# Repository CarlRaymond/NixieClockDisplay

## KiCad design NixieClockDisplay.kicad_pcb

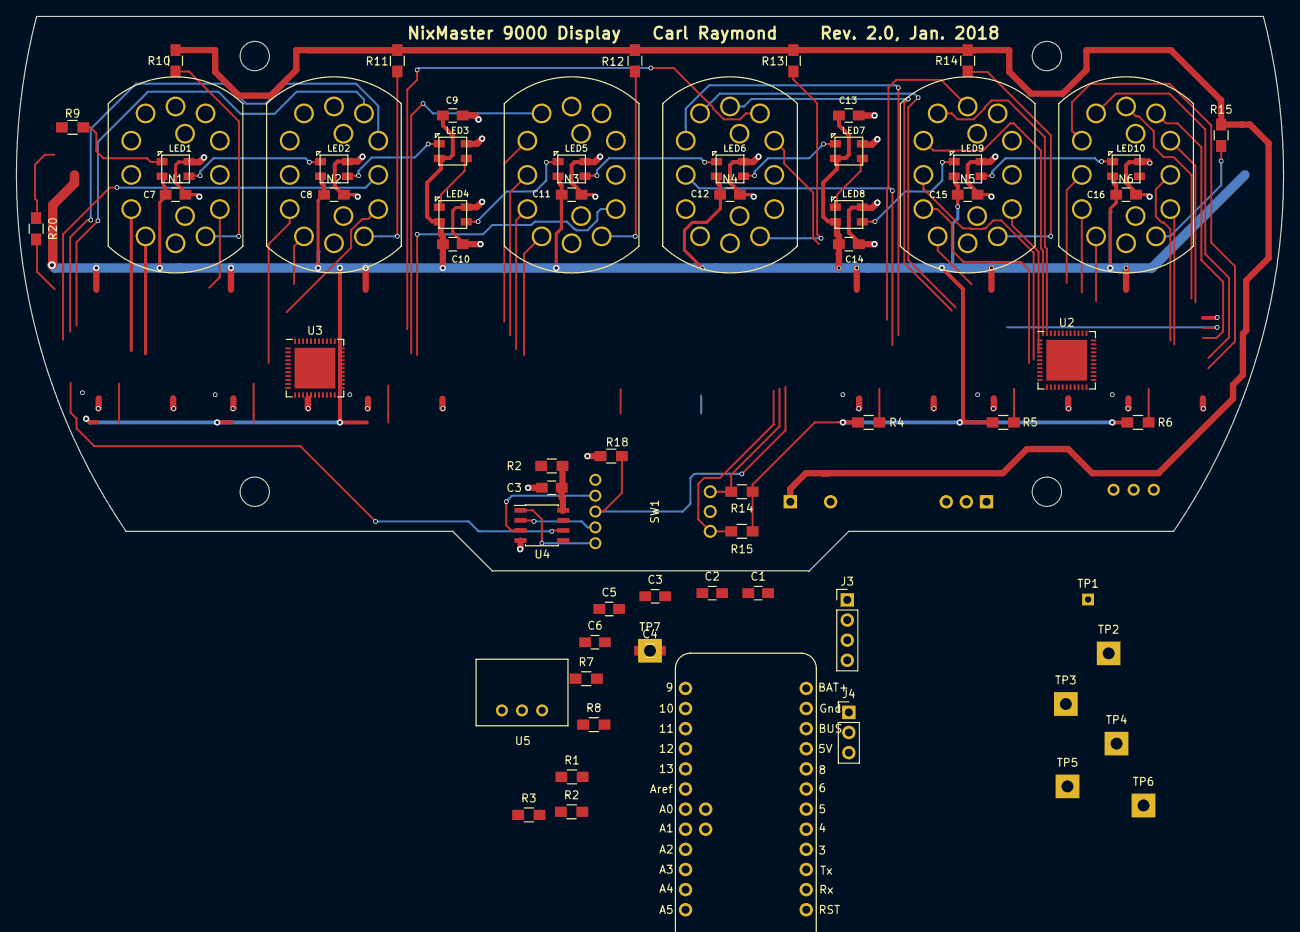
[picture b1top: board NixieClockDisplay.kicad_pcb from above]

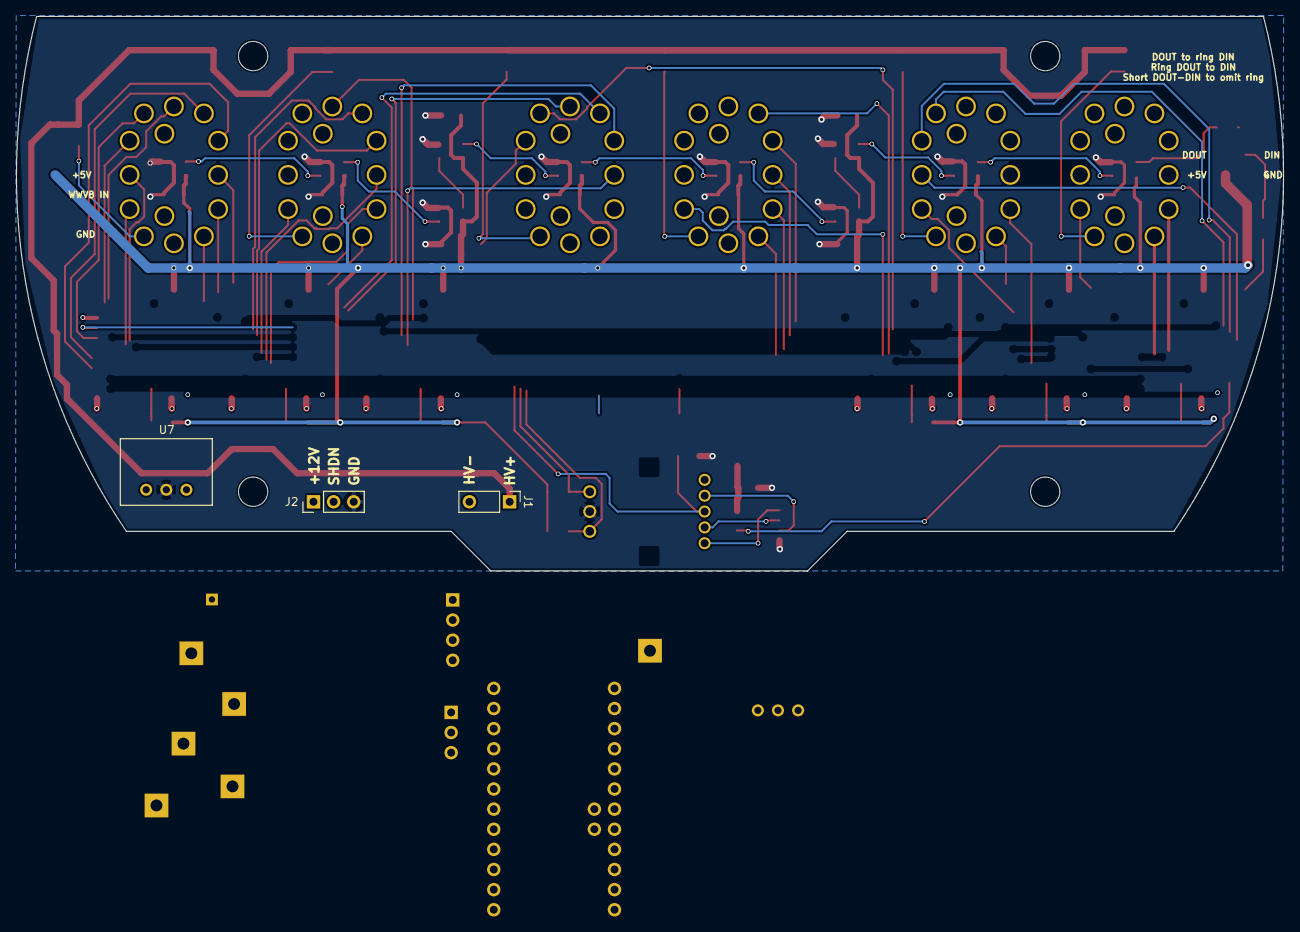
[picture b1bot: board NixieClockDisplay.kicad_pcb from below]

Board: 2 copper layers, 160.0 x 70.0 mm, 71 parts (3 on the bottom side), 102 nets.

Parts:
C1, C2, C3, C3#2, C4, C5, C6, C7, C8, C9, C10, C11, C12, C13, C14, C15, C16: .1uF; C_0805_HandSoldering
J1: CONN_01X02; Pin_Header_Straight_1x03_Pitch2.54mm_No_Center
J2: CONN_01X03; Pin_Header_Straight_1x03_Pitch2.54mm
J3: Conn_01x04; Pin_Header_Straight_1x04_Pitch2.54mm
J4: Conn_01x03; Pin_Header_Straight_1x03_Pitch2.54mm
LED1, LED2, LED3, LED4, LED5, LED6, LED7, LED8, LED9, LED10: SK6812MINI; LED_3535_4pin
N1, N2, N3, N4, N5, N6: Nixie; Socket_SK-136
R1, R20: 33R; R_0805_HandSoldering
R2, R2#2: 100; R_0805_HandSoldering
R3, R5, R7, R18: 10K; R_0805_HandSoldering
R4, R6, R8, R10, R11, R12, R13, R14, R14#2, R15, R15#2: 22K; R_0805_HandSoldering
R9: 470; R_0805_HandSoldering
SW1: RotaryEncoder_Switch_RGB; EC12PLRGB_Rotary_Encoder
TP1: TEST_1P; Measurement_Point_Square-TH_Small
TP2, TP3, TP4, TP5, TP6, TP7: TEST_1P; Measurement_Point_Square-TH_Big
U1: AdafruitProTrinket5V; Adafruit_Trinket_Pro
U2, U3: HV5523; QFN-44-1EP_7x7mm_Pitch0.5mm
U4: WS2811; SOIC-8_3.9x4.9mm_Pitch1.27mm
U5, U7: WE-FDSM_DC/DC_5V; WPMDL9500xx

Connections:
60HZ_OUT: TP3.1, U1.18
+5V: C1.1, C2.1, C7.2, C8.2, C9.2, C10.2, C11.2, C12.2, C13.2, C14.2, C15.2, C16.2, J3.1, J4.1, LED1.4, LED2.4, LED3.4, LED4.4, LED5.4, LED6.4, LED7.4, LED8.4, LED9.4, LED10.4, R2.2, R2#2.2, R5.1, R7.1, SW1.5, TP1.1, U2.27, U2.30, U3.27, U3.30, U5.3, U7.3
+12V: J2.1, TP2.1, U1.24, U5.1, U7.1
+180V: J1.1, R10.2, R11.2, R12.2, R13.2, R14.2, R14#2.2, R15.2, R15#2.2
/NIXIE_LE: TP6.1, U1.1, U2.31, U3.31
GND: C1.2, C2.2, C3.2, C3#2.2, C4.2, C5.2, C6.2, C7.1, C8.1, C9.1, C10.1, C11.1, C12.1, C13.1, C14.1, C15.1, C16.1, J1.2, J2.3, J3.3, J3.4, J4.2, LED1.2, LED2.2, LED3.2, LED4.2, LED5.2, LED6.2, LED7.2, LED8.2, LED9.2, LED10.2, R3.1, R18.1, SW1.C, U1.23, U2.29, U3.29, U4.4, U5.2, U7.2
HOUR_0: N2.2, U3.1
HOUR_00: N1.2, U3.11
HOUR_1: N2.11, U3.2
HOUR_2: N2.10, U3.3
HOUR_3: N2.9, U3.4
HOUR_4: N2.8, U3.5
HOUR_5: N2.7, U3.6
HOUR_6: N2.6, U3.7
HOUR_7: N2.5, U3.8
HOUR_8: N2.4, U3.9
HOUR_9: N2.3, U3.10
HOUR_10: N1.11, U3.12
HOUR_20: N1.10, U3.13
HOUR_30: N1.9, U3.14
HOUR_40: N1.8, U3.15
HOUR_50: N1.7, U3.16
HOUR_60: N1.6, U3.17
HOUR_70: N1.5, U3.18
HOUR_80: N1.4, U3.19
HOUR_90: N1.3, U3.20
MIN_0: N4.2, U2.11
MIN_00: N3.2, U3.35
MIN_1: N4.11, U2.12
MIN_2: N4.10, U2.13
MIN_3: N4.9, U2.14
MIN_4: N4.8, U2.15
MIN_5: N4.7, U2.16
MIN_6: N4.6, U2.17
MIN_7: N4.5, U2.18
MIN_8: N4.4, U2.19
MIN_9: N4.3, U2.20
MIN_10: N3.11, U3.36
MIN_20: N3.10, U3.37
MIN_30: N3.9, U3.38
MIN_40: N3.8, U3.39
MIN_50: N3.7, U3.40
MIN_60: N3.6, U3.41
MIN_70: N3.5, U3.42
MIN_80: N3.4, U3.43
MIN_90: N3.3, U3.44
NIXIE_BLANK: TP7.1, U1.17, U2.33, U3.33
NIXIE_CLK: TP5.1, U1.5, U2.28, U3.28
NIXIE_DATA: TP4.1, U1.3, U2.32
unnamed: C3.1, C3#2.1, R2.1, R2#2.1, U4.8
unnamed: J4.3, LED10.1
unnamed: LED1.1, LED2.3
unnamed: LED1.3, R9.1
unnamed: LED2.1, LED3.3
unnamed: LED3.1, LED4.3
unnamed: LED4.1, LED5.3
unnamed: LED5.1, LED6.3
unnamed: LED6.1, LED7.3
unnamed: LED7.1, LED8.3
unnamed: LED8.1, LED9.3
unnamed: LED9.1, LED10.3
unnamed: N1.1, R10.1
unnamed: N2.1, R11.1
unnamed: N3.1, R12.1
unnamed: N4.1, R13.1
unnamed: N5.1, R14.1, R14#2.1
unnamed: N6.1, R15.1, R15#2.1
unnamed: R1.2, U4.6
unnamed: R3.2, R4.2, SW1.3
unnamed: R5.2, R6.2, SW1.A
unnamed: R7.2, R8.2, SW1.B
unnamed: R9.2, U4.5
unnamed: SW1.1, U4.1
unnamed: SW1.2, U4.2
unnamed: SW1.4, U4.3
unnamed: U2.23, U3.32
PIXEL_DATA: R1.1, U1.19
ROTARY_A: C5.1, R6.1, U1.7
ROTARY_B: C6.1, R8.1, U1.8
ROTARY_PB: C4.1, R4.1, U1.9
SEC_00: N5.2, U2.1
SEC_0: N6.2, U2.35
SEC_1: N6.11, U2.36
SEC_2: N6.10, U2.37
SEC_3: N6.9, U2.38
SEC_4: N6.8, U2.39
SEC_5: N6.7, U2.40
SEC_6: N6.6, U2.41
SEC_7: N6.5, U2.42
SEC_8: N6.4, U2.43
SEC_9: N6.3, U2.44
SEC_10: N5.11, U2.2
SEC_20: N5.10, U2.3
SEC_30: N5.9, U2.4
SEC_40: N5.8, U2.5
SEC_50: N5.7, U2.6
SEC_60: N5.6, U2.7
SEC_70: N5.5, U2.8
SEC_80: N5.4, U2.9
SEC_90: N5.3, U2.10
SHDN: J2.2, U1.16
TIME_IN: J3.2, U1.20

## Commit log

2017-06-05 Begin board layout
2017-06-06 Fiddling.
2017-06-08 More layout
2017-06-09 Moar traces
2017-06-12 Rotating driver chips
2017-06-12 Much routing
2017-06-13 Moved 5V bus.
2017-06-14 Rotated driver chips
2017-06-15 Near complete layout
2017-06-16 Routing complete
2017-06-16 Added mounting holes
2017-06-17 Moved mounting holes
2017-06-17 Moved tracks away from mounting holes
2017-06-17 Curved board outline
2017-06-18 Finalized board
2017-06-18 More finalzed.
2017-06-18 Arranged connectors to mate with NixiePowerSupply board.
2017-06-18 Final board.
2017-11-24 Updated anode resistors; changed pin header orientation after KiCad update
2017-11-28 Add Adafruit Trinket and rotary encoder.
2017-12-26 Begin layout
2018-01-16 Add Adafruit Trinket Pro, rotary switch
2018-01-18 Add datasheets; redraw schematic with HV5522.
2018-01-22 Replace HV5522 with HV5523
2018-01-27 Schematic complete
2018-04-25 Add Adafruit OLED display
2018-04-28 Reassign PWM and TIME_IN pins
